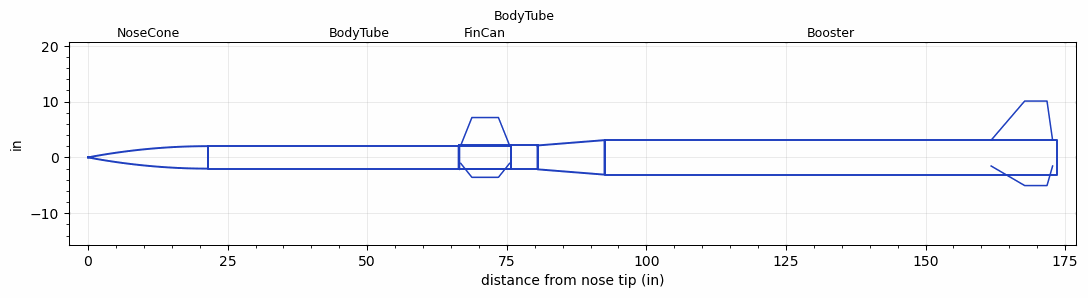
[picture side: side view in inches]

<RASAeroDocument>
 <FileVersion>2</FileVersion>
 <RocketDesign>
  <NoseCone>
   <Length>21.5</Length>
   <Diameter>4.026</Diameter>
   <Shape>Tangent Ogive</Shape>
   <BluntRadius>0.125</BluntRadius>
   <Location>0</Location>
  </NoseCone>
  <BodyTube>
   <Length>54.25</Length>
   <Diameter>4.026</Diameter>
   <Location>21.5</Location>
  </BodyTube>
  <FinCan>
   <Length>9.25</Length>
   <Diameter>4.276</Diameter>
   <InsideDiameter>4.026</InsideDiameter>
   <Location>75.75</Location>
   <ShoulderLength>0.125</ShoulderLength>
   <Offset>-9.25</Offset>
   <Fin>
    <Count>3</Count>
    <Chord>8.75</Chord>
    <Span>5</Span>
    <SweepDistance>2</SweepDistance>
    <TipChord>4.75</TipChord>
    <Thickness>0.125</Thickness>
    <LERadius>0.0625</LERadius>
    <Location>9</Location>
    <AirfoilSection>Hexagonal</AirfoilSection>
    <FX1>0.5</FX1>
    <FX3>0.5</FX3>
   </Fin>
  </FinCan>
  <BodyTube>
   <Length>4.75</Length>
   <Diameter>4.276</Diameter>
   <Location>75.75</Location>
  </BodyTube>
  <Booster>
   <Length>81</Length>
   <Diameter>6.18</Diameter>
   <InsideDiameter>4.276</InsideDiameter>
   <RailGuideDiameter>1.25</RailGuideDiameter>
   <RailGuideHeight>1</RailGuideHeight>
   <Location>80.5</Location>
   <ShoulderLength>12</ShoulderLength>
   <Fin>
    <Count>3</Count>
    <Chord>11</Chord>
    <Span>7</Span>
    <SweepDistance>6</SweepDistance>
    <TipChord>4</TipChord>
    <Thickness>0.125</Thickness>
    <LERadius>0.0625</LERadius>
    <Location>11.75</Location>
    <AirfoilSection>Hexagonal</AirfoilSection>
    <FX1>0.5</FX1>
    <FX3>0.5</FX3>
   </Fin>
  </Booster>
  <Surface>Rough Camouflage Paint</Surface>
  <ModifiedBarrowman>True</ModifiedBarrowman>
  <Turbulence>True</Turbulence>
  <UseBooster1>False</UseBooster1>
  <UseBooster2>False</UseBooster2>
 </RocketDesign>
 <LaunchSite>
  <Altitude>50</Altitude>
  <Pressure>0</Pressure>
  <RodAngle>1</RodAngle>
  <RodLength>15</RodLength>
  <Temperature>70</Temperature>
  <WindSpeed>10</WindSpeed>
 </LaunchSite>
 <Recovery>
  <Altitude1>1000</Altitude1>
  <Altitude2>1000</Altitude2>
  <DeviceType1>None</DeviceType1>
  <DeviceType2>None</DeviceType2>
  <Event1>False</Event1>
  <Event2>False</Event2>
  <Size1>1</Size1>
  <Size2>1</Size2>
  <EventType1>None</EventType1>
  <EventType2>None</EventType2>
  <CD1>1.33</CD1>
  <CD2>1.33</CD2>
 </Recovery>
 <SimulationList>
  <Simulation>
   <SustainerEngine>K735-SK-P  (CTI)</SustainerEngine>
   <SustainerLaunchWt>26.5</SustainerLaunchWt>
   <SustainerNozzleDiameter>2.75</SustainerNozzleDiameter>
   <SustainerCG>55</SustainerCG>
   <SustainerIgnitionDelay>2</SustainerIgnitionDelay>
   <Booster1Engine>M3400-WT  (CTI)</Booster1Engine>
   <Booster1LaunchWt>83</Booster1LaunchWt>
   <Booster1SeparationDelay>0.5</Booster1SeparationDelay>
   <Booster1IgnitionDelay>0</Booster1IgnitionDelay>
   <Booster1CG>110</Booster1CG>
   <Booster1NozzleDiameter>3.625</Booster1NozzleDiameter>
   <IncludeBooster1>True</IncludeBooster1>
   <Booster2Delay>0</Booster2Delay>
   <IncludeBooster2>True</IncludeBooster2>
   <TimetoApogee>30.66052</TimetoApogee>
   <MaxAltitude>14670.2</MaxAltitude>
   <MaxVelocity>1037.543</MaxVelocity>
  </Simulation>
  <Simulation>
   <SustainerEngine>K735-SK-P  (CTI)</SustainerEngine>
   <SustainerLaunchWt>26.5</SustainerLaunchWt>
   <SustainerNozzleDiameter>2.75</SustainerNozzleDiameter>
   <SustainerCG>55</SustainerCG>
   <SustainerIgnitionDelay>2</SustainerIgnitionDelay>
   <Booster1Engine>M2505  (CTI)</Booster1Engine>
   <Booster1LaunchWt>79</Booster1LaunchWt>
   <Booster1SeparationDelay>0.5</Booster1SeparationDelay>
   <Booster1IgnitionDelay>0</Booster1IgnitionDelay>
   <Booster1CG>108</Booster1CG>
   <Booster1NozzleDiameter>3.625</Booster1NozzleDiameter>
   <IncludeBooster1>True</IncludeBooster1>
   <Booster2Delay>0</Booster2Delay>
   <IncludeBooster2>False</IncludeBooster2>
   <TimetoApogee>28.70048</TimetoApogee>
   <MaxAltitude>11759.97</MaxAltitude>
   <MaxVelocity>900.1909</MaxVelocity>
  </Simulation>
  <Simulation>
   <SustainerEngine>K510  (CTI)</SustainerEngine>
   <SustainerLaunchWt>26.5</SustainerLaunchWt>
   <SustainerNozzleDiameter>2.75</SustainerNozzleDiameter>
   <SustainerCG>55</SustainerCG>
   <SustainerIgnitionDelay>2</SustainerIgnitionDelay>
   <Booster1Engine>M2505  (CTI)</Booster1Engine>
   <Booster1LaunchWt>79</Booster1LaunchWt>
   <Booster1SeparationDelay>0.5</Booster1SeparationDelay>
   <Booster1IgnitionDelay>0</Booster1IgnitionDelay>
   <Booster1CG>108</Booster1CG>
   <Booster1NozzleDiameter>3.625</Booster1NozzleDiameter>
   <IncludeBooster1>True</IncludeBooster1>
   <Booster2Delay>0</Booster2Delay>
   <IncludeBooster2>False</IncludeBooster2>
   <TimetoApogee>31.59054</TimetoApogee>
   <MaxAltitude>14077.13</MaxAltitude>
   <MaxVelocity>941.4681</MaxVelocity>
  </Simulation>
  <Simulation>
   <SustainerEngine>K510  (CTI)</SustainerEngine>
   <SustainerLaunchWt>26.5</SustainerLaunchWt>
   <SustainerNozzleDiameter>2.75</SustainerNozzleDiameter>
   <SustainerCG>55</SustainerCG>
   <SustainerIgnitionDelay>2</SustainerIgnitionDelay>
   <Booster1Engine>M3400-WT  (CTI)</Booster1Engine>
   <Booster1LaunchWt>83</Booster1LaunchWt>
   <Booster1SeparationDelay>0.5</Booster1SeparationDelay>
   <Booster1IgnitionDelay>0</Booster1IgnitionDelay>
   <Booster1CG>110</Booster1CG>
   <Booster1NozzleDiameter>3.625</Booster1NozzleDiameter>
   <IncludeBooster1>True</IncludeBooster1>
   <Booster2Delay>0</Booster2Delay>
   <IncludeBooster2>False</IncludeBooster2>
   <TimetoApogee>33.28058</TimetoApogee>
   <MaxAltitude>17026.58</MaxAltitude>
   <MaxVelocity>1053.922</MaxVelocity>
  </Simulation>
  <Simulation>
   <SustainerEngine>K510  (CTI)</SustainerEngine>
   <SustainerLaunchWt>26.5</SustainerLaunchWt>
   <SustainerNozzleDiameter>2.75</SustainerNozzleDiameter>
   <SustainerCG>55</SustainerCG>
   <SustainerIgnitionDelay>2</SustainerIgnitionDelay>
   <Booster1Engine>M2075-SS  (CTI)</Booster1Engine>
   <Booster1LaunchWt>81</Booster1LaunchWt>
   <Booster1SeparationDelay>0.5</Booster1SeparationDelay>
   <Booster1IgnitionDelay>0</Booster1IgnitionDelay>
   <Booster1CG>107</Booster1CG>
   <Booster1NozzleDiameter>3.625</Booster1NozzleDiameter>
   <IncludeBooster1>True</IncludeBooster1>
   <Booster2Delay>0</Booster2Delay>
   <IncludeBooster2>False</IncludeBooster2>
   <TimetoApogee>30.46052</TimetoApogee>
   <MaxAltitude>12412.74</MaxAltitude>
   <MaxVelocity>870.8581</MaxVelocity>
  </Simulation>
 </SimulationList>
</RASAeroDocument>
